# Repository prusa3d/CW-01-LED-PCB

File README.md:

# PRUSA CW-01 LED board

KiCad PCB layout

* [Interactive bom](http://htmlpreview.github.io/?https://github.com/prusa3d/CW-01-LED-PCB/blob/master/rev.01c/ibom.html)
* [STEP 3D model](rev.01c/led-panel.step)

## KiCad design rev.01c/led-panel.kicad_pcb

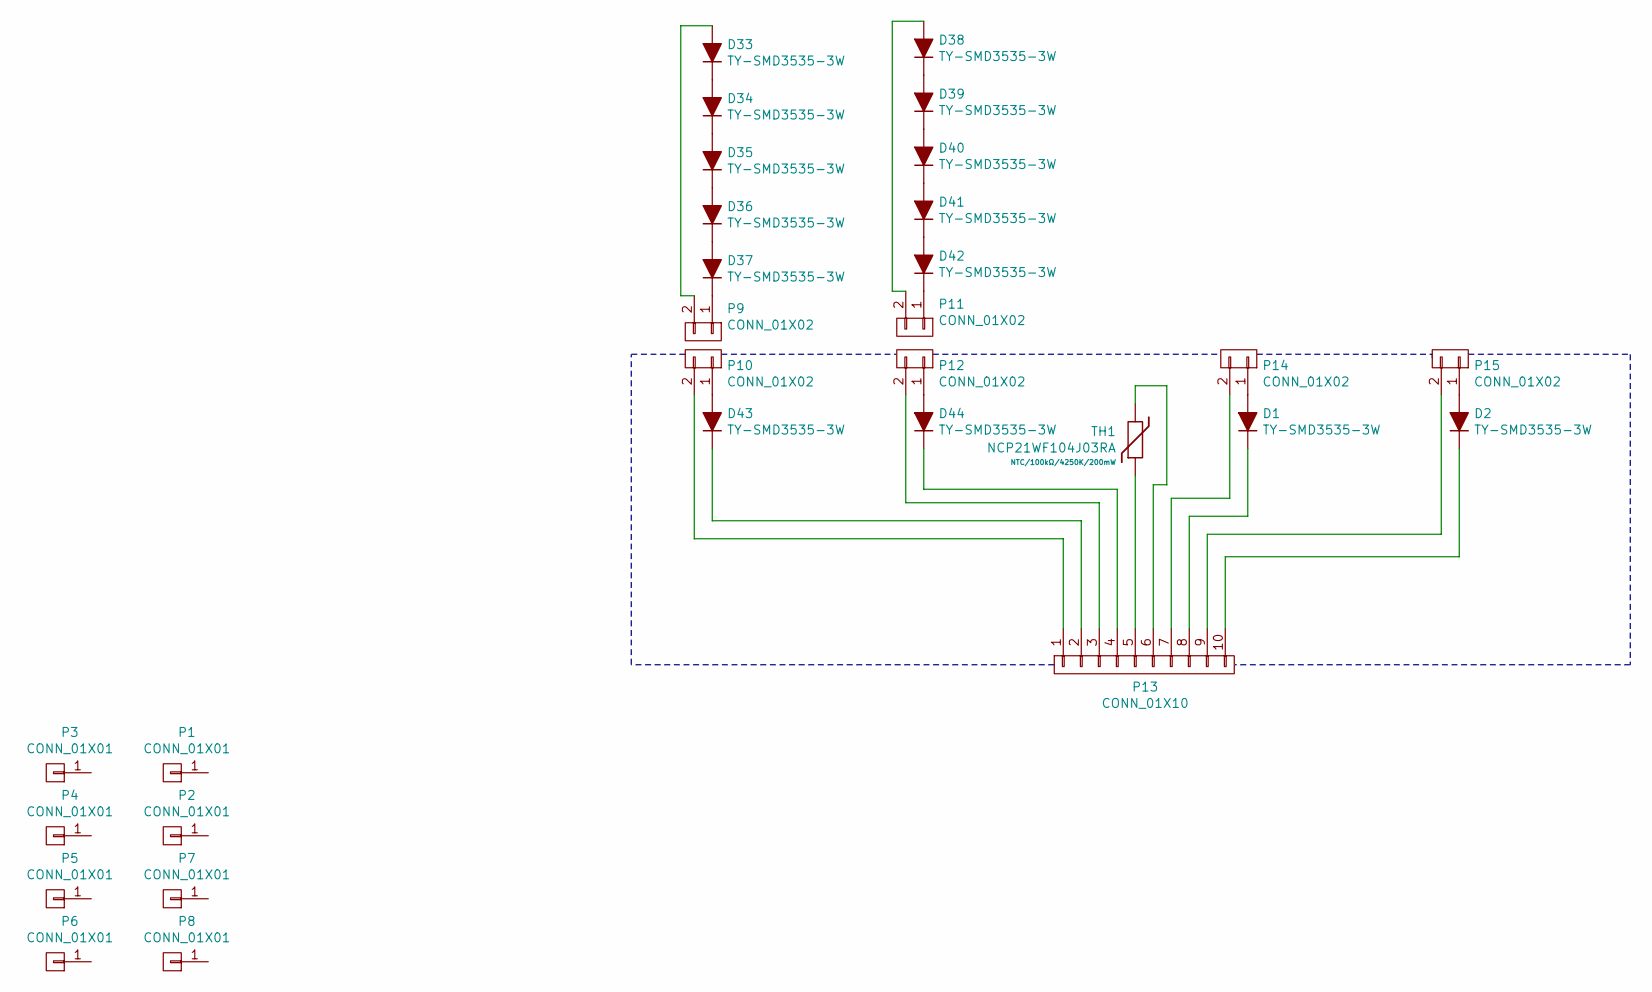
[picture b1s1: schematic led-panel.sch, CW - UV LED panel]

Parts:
D1, D2, D33, D34, D35, D36, D37, D38, D39, D40, D41, D42, D43, D44: TY-SMD3535-3W; LED-UV-LTPL-C034UVH405
P1, P2, P3, P4, P5, P6, P7, P8: CONN_01X01; MountingHole_4.5mm
P9, P10, P11, P12, P14, P15: CONN_01X02; MX-172159-0602
P13: CONN_01X10; MX-172159-0610
TH1: NCP21WF104J03RA; R_0805

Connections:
unnamed: D1.1 (K), P13.8
unnamed: D1.2 (A), P14.1
unnamed: D2.1 (K), P13.10
unnamed: D2.2 (A), P15.1
unnamed: D33.1 (K), D34.2 (A)
unnamed: D33.2 (A), P9.2
unnamed: D34.1 (K), D35.2 (A)
unnamed: D35.1 (K), D36.2 (A)
unnamed: D36.1 (K), D37.2 (A)
unnamed: D37.1 (K), P9.1
unnamed: D38.1 (K), D39.2 (A)
unnamed: D38.2 (A), P11.2
unnamed: D39.1 (K), D40.2 (A)
unnamed: D40.1 (K), D41.2 (A)
unnamed: D41.1 (K), D42.2 (A)
unnamed: D42.1 (K), P11.1
unnamed: D43.1 (K), P13.2
unnamed: D43.2 (A), P10.1
unnamed: D44.1 (K), P13.4
unnamed: D44.2 (A), P12.1
unnamed: P10.2, P13.1
unnamed: P12.2, P13.3
unnamed: P13.5, TH1.1
unnamed: P13.6, TH1.2
unnamed: P13.7, P14.2
unnamed: P13.9, P15.2

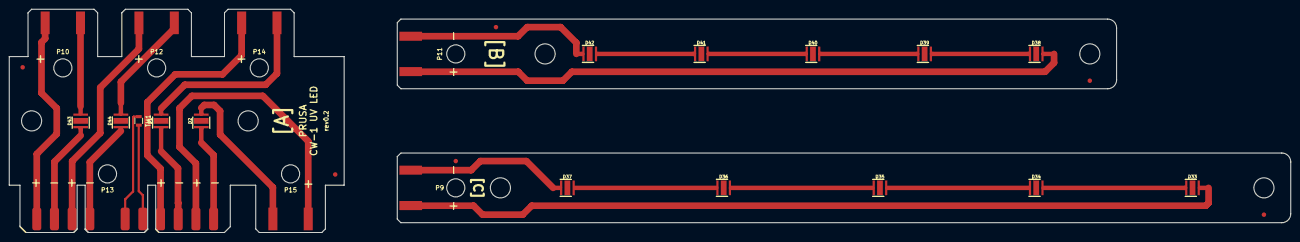
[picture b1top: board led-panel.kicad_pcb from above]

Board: 2 copper layers, 287.0 x 50.0 mm, 28 parts (0 on the bottom side), 26 nets.

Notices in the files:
rev.01c/led-panel.sch:
http://creativecommons.org/licenses/by-sa/4.0
Licensed under the Attribution-ShareAlike 4.0 International (CC BY-SA 4.0)
